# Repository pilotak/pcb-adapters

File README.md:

# Collection of SMD to breadboard adapters
When you manufature PCB in China, you usually have a space left over so why not fill it with some useful adapters!

## MSOP8/TSSOP8 adapter

## SOIC8/SOIC8W adapter

## SOIC14/SOIC14L adapter

## SOIC16/SOIC16L adapter

## SOIC18/SOIC18L adapter

## SOT363 adapter

## SOT23-6 adapter

## RJ11 adapter

## RJ45 adapter

*PCBs done in Eagle 8*

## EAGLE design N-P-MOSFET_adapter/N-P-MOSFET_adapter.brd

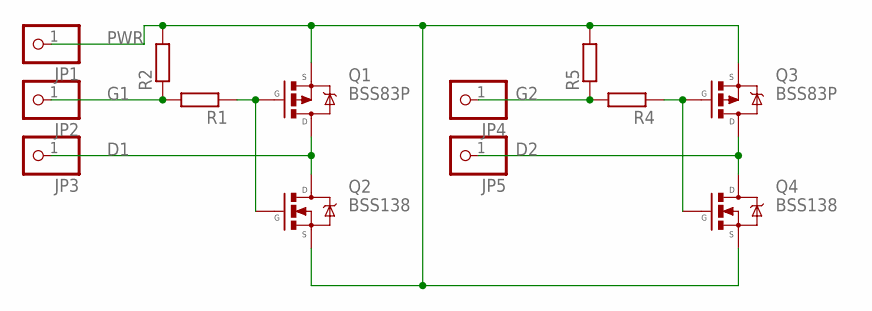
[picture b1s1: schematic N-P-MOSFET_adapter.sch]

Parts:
JP1, JP2, JP3, JP4, JP5: PINHD-1X1JUST_PIN; 1X01_BARE
Q1, Q3: BSS83P; SOT23
Q2, Q4: BSS138; SOT23
R1, R2, R4, R5: R-EU_R0805; R0805

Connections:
D1: JP3.1, Q1.3 (D), Q2.3 (D)
D2: JP5.1, Q3.3 (D), Q4.3 (D)
G1: JP2.1, R1.2, R2.1
G2: JP4.1, R4.2, R5.1
unnamed: Q1.1 (G), Q2.1 (G), R1.1
unnamed: Q3.1 (G), Q4.1 (G), R4.1
PWR: JP1.1, Q1.2 (S), Q2.2 (S), Q3.2 (S), Q4.2 (S), R2.2, R5.2

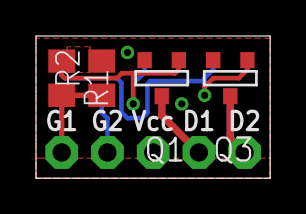
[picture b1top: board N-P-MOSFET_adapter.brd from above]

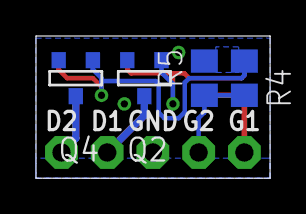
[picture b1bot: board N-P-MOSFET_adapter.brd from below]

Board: 2 copper layers, 13.0 x 7.9 mm, 13 parts (9 on the bottom side), 7 nets.

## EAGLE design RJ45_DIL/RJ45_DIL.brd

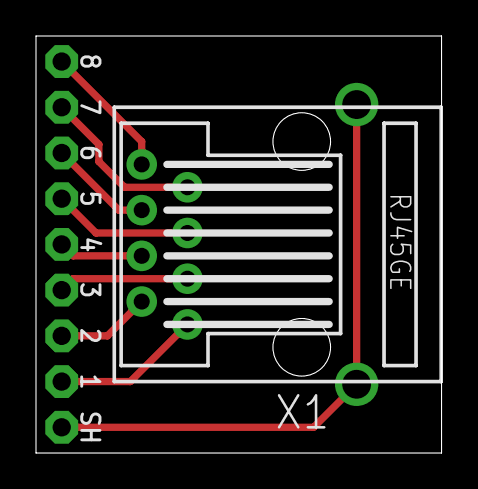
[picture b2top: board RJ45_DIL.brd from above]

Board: 2 copper layers, 22.5 x 23.2 mm, 10 parts (0 on the bottom side), 9 nets.

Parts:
JP1, JP2, JP3, JP4, JP5, JP6, JP7, JP8, JP9: 1X01_BARE
X1: RJ-45-SHIELDED; RJ45GE

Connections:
1: JP1.1, X1.1
2: JP2.1, X1.2
3: JP3.1, X1.3
4: JP4.1, X1.4
5: JP5.1, X1.5
6: JP6.1, X1.6
7: JP7.1, X1.7
8: JP8.1, X1.8
unnamed: JP9.1, X1.SHIELD1, X1.SHIELD2

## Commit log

2017-09-13 N/P mosfet adapter
2017-09-13 image align
2017-09-14 N/P mosfet RG adapter
2017-09-14 schematic
2017-09-14 img correction
2018-01-14 new adapters
2018-01-14 msop/tssop update
2018-01-14 N/P mosfet delete
2018-02-09 sot23 + (soic8 & sot363 fix)
2018-03-07 licence change
